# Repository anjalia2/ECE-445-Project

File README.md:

# Circle of Life: Automated Desktop Aquaponics System

## Team Members: Anjali Aravindhan, Aishwarya Manoj, Estela Medrano-Gutierrez

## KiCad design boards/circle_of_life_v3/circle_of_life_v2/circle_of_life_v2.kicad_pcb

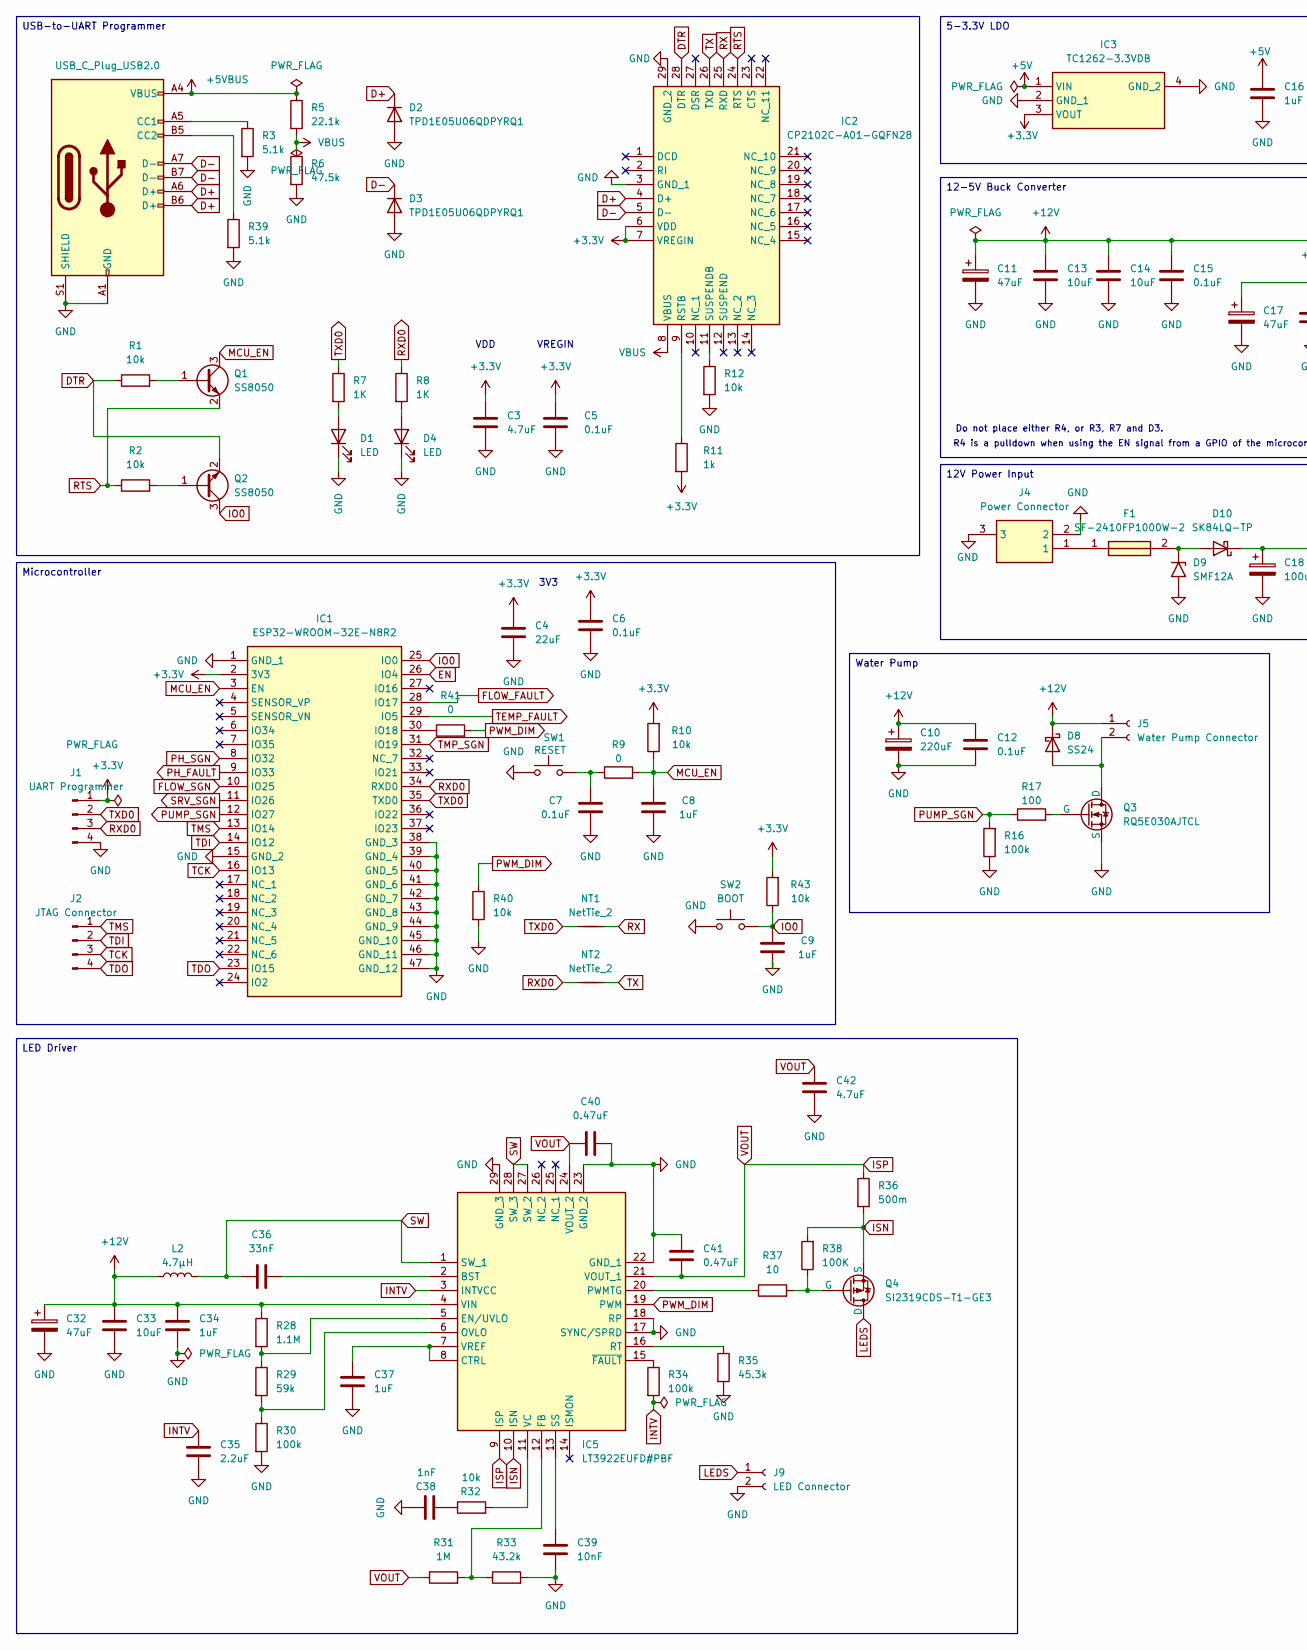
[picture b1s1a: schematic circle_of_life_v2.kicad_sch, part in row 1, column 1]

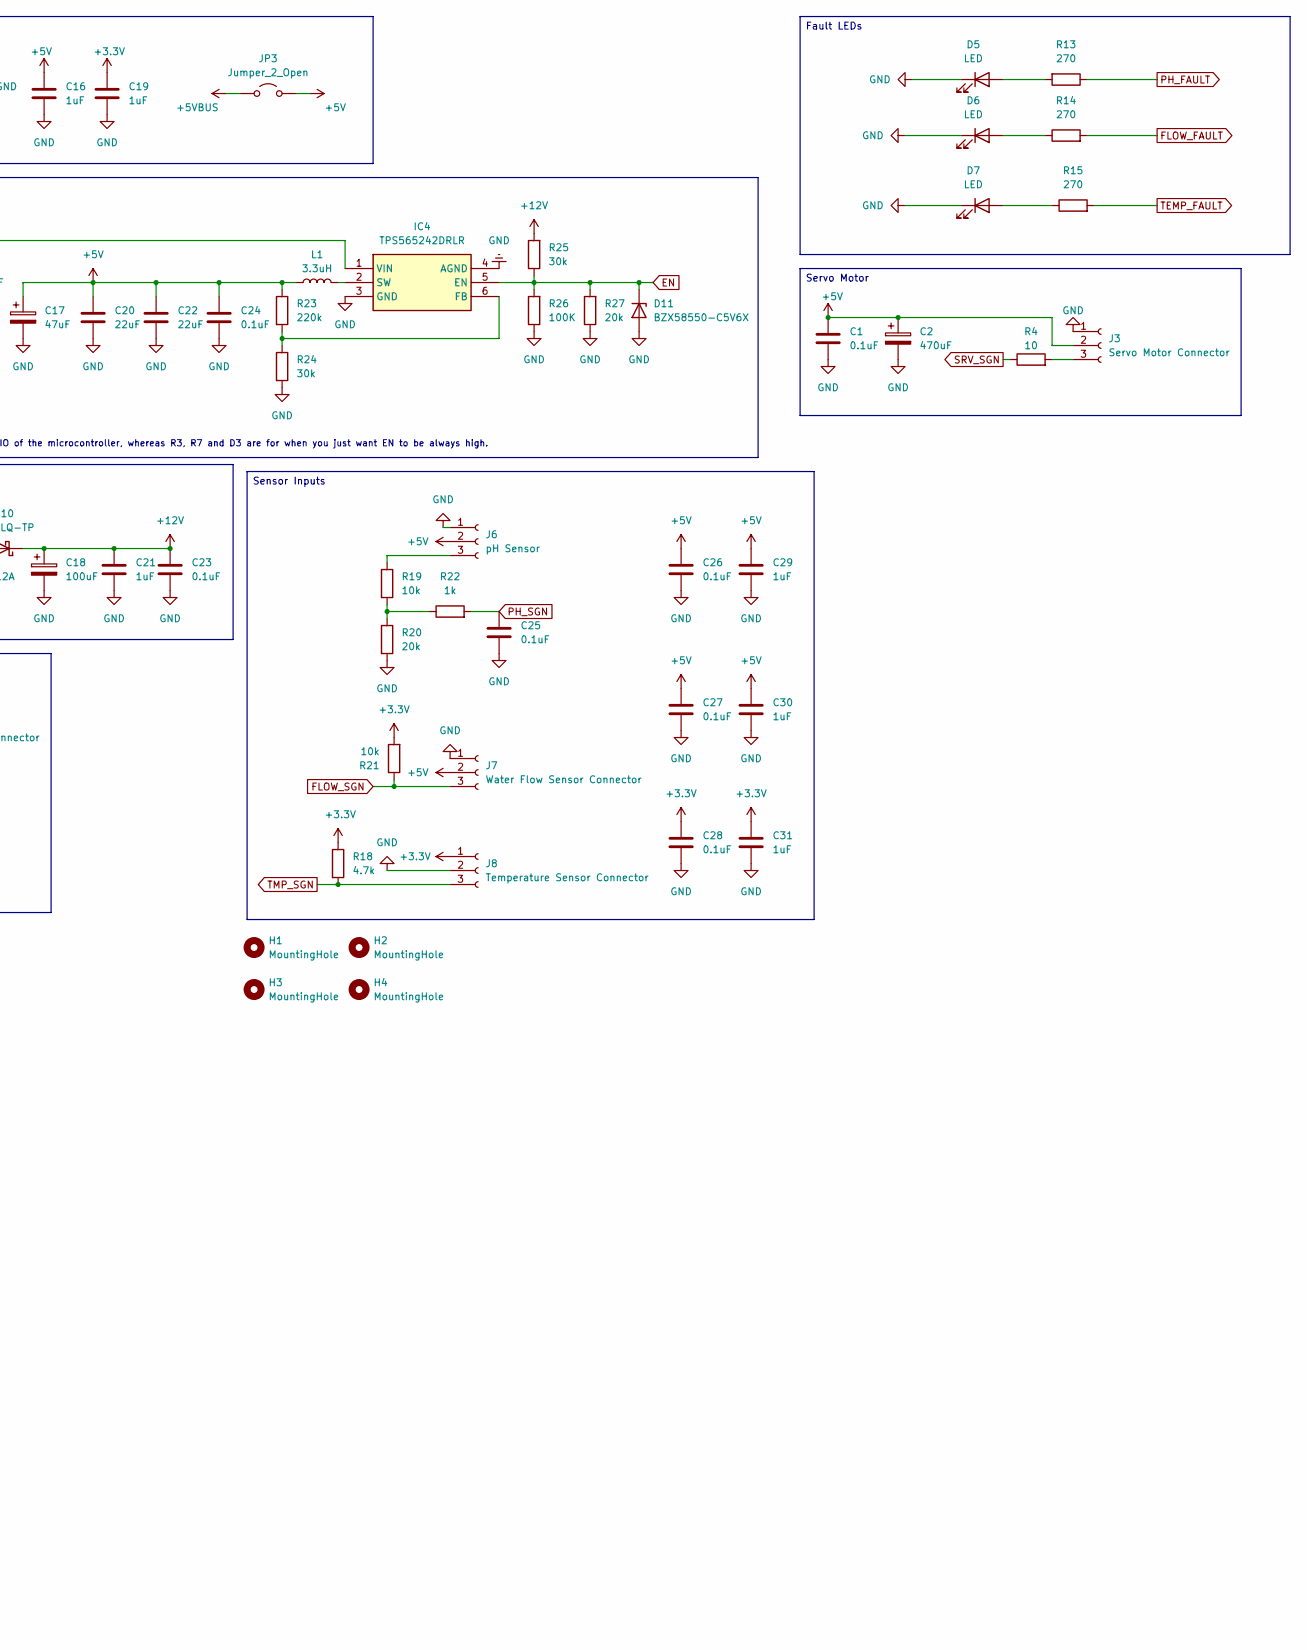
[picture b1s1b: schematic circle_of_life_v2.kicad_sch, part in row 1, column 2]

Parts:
C1, C5, C6, C7, C12, C23, C24, C25, C26, C27, C28: 0.1uF; C_0805_2012Metric
C2: 470uF; CAPPRD500W60D1025H1400
C3, C42: 4.7uF; C_0805_2012Metric
C4, C20, C22: 22uF; CAPC3216X190N
C8, C9, C16, C19, C21, C29, C30, C31, C34, C37: 1uF; C_0805_2012Metric
C10: 220uF; CAPPRD350W60D825H1300
C11, C17, C32: 47uF; CAPPRD250W50D655H1250
C13, C14: 10uF; C_0805_2012Metric
C15: 0.1uF; C_0805_2012Metric_Pad1.18x1.45mm_HandSolder
C18: 100uF; CAPAE630X800N
C33: 10uF; R_0805_2012Metric_Pad1.20x1.40mm_HandSolder
C35: 2.2uF; CAPC1608X90N
C36: 33nF; 0805_AVX
C38: 1nF; C_0805_2012Metric
C39: 10nF; C_0603_1608Metric
C40, C41: 0.47uF; GRM15x
D1, D4: LED; LED_0603_1608Metric
D2, D3: TPD1E05U06QDPYRQ1; DPY_R-PX1SON-N2_
D5, D6, D7: LED; LED_D5.0mm
D8: SS24; DIOM5436X247N
D9: SMF12A; TVS_SMF12A
D10: SK84LQ-TP; DIOM7959X262N
D11: BZX58550-C5V6X; D_SOD-523
F1: SF-2410FP1000W-2; FUSC6125X236N; Mouser Part Number 652-SF-2410FP1000W-2
H1, H2, H3, H4: MountingHole; MountingHole_3.2mm_M3_ISO7380
IC1: ESP32-WROOM-32E-N8R2; ESP32WROOM32EN8R2; Mouser Part Number 356-ESP32WRM32EN8R2
IC2: CP2102C-A01-GQFN28; QFN50P500X500X80-29N-D; Mouser Part Number 634-P2102CA01GQFN28
IC3: TC1262-3.3VDB; SOT230P700X180-4N; Mouser Part Number 579-TC1262-3.3VDB
IC4: TPS565242DRLR; SOTFL50P160X60-6N; Mouser Part Number 595-TPS565242DRLR
IC5: LT3922EUFD#PBF; QFN50P400X500X80-29N-D; Mouser Part Number 584-LT3922EUFD#PBF
J1: UART Programmer; PinHeader_1x04_P2.54mm_Vertical
J2: JTAG Connector; PinHeader_1x04_P2.54mm_Vertical
J3: Servo Motor Connector; 691137710003
J4: Power Connector; 694108301002; Mouser Part Number 710-694108301002
J5: Water Pump Connector; 2828372
J6: pH Sensor; 691137710003
J7: Water Flow Sensor Connector; 691137710003
J8: Temperature Sensor Connector; 691137710003
J9: LED Connector; 2828372
JP3: Jumper_2_Open; SolderJumper-2_P1.3mm_Open_RoundedPad1.0x1.5mm
L1: 3.3uH; INDC4949X330N
L2: 4.7µH; SRN6045_1
NT1, NT2: NetTie_2; NetTie-2_SMD_Pad0.5mm
P1: USB_C_Plug_USB2.0; USB_C_Receptacle_HRO_TYPE-C-31-M-12
Q1, Q2: SS8050; SOT-23
Q3: RQ5E030AJTCL; SOT95P280X100-3N
Q4: SI2319CDS-T1-GE3; SOT95P237X112-3N
R1, R2, R12, R43: 10k; R_0603_1608Metric
R3, R39: 5.1k; R_0603_1608Metric
R4, R37: 10; RESC1608X55N
R5: 22.1k; R_0603_1608Metric
R6: 47.5k; R_0603_1608Metric
R7, R8: 1K; RESC1608X55N
R9, R41: 0; RESC1608X55N
R10, R19, R21, R32, R40: 10k; RESC1608X55N
R11: 1k; R_0603_1608Metric
R13, R14, R15: 270; RESC1608X55N
R16, R34: 100k; RESC1608X55N
R17: 100; RESC1608X55N
R18: 4.7k; RESC1608X55N
R20: 20k; RESC1608X55N
R22: 1k; RESC1608X55N
R23: 220k; RESC2012X60N
R24: 30k; RESC2012X60N
R25: 30k; R_0805_2012Metric
R26: 100K; RESC2012X60N
R27: 20k; RESC2012X60N
R28: 1.1M; RESC3116X65N
R29: 59k; RESC2012X60N
R30: 100k; RESC2012X60N
R31: 1M; RESC1608X55N
R33: 43.2k; RESC1608X55N
R35: 45.3k; RESC1608X55N
R36: 500m; CSR1206
R38: 100K; RESC1608X55N
SW1: RESET; SW_SPST_SKQG_WithStem
SW2: BOOT; SW_SPST_SKQG_WithStem

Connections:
+3.3V: C3.1, C4.1, C5.1, C6.1, C19.1, C28.1, C31.1, IC1.2 (3V3), IC2.6 (VDD), IC2.7 (VREGIN), IC3.3 (VOUT), J1.1, J8.1, R10.2, R11.2, R18.1, R21.2, R43.2
+5V: C1.1, C2.1, C16.1, C17.1, C20.1, C22.1, C24.1, C26.1, C27.1, C29.1, C30.1, IC3.1 (VIN), J3.2, J6.2, J7.2, JP3.2 (B), L1.1, R23.1
+5VBUS: JP3.1 (A), P1.A4 (VBUS), P1.A9 (VBUS), P1.B4 (VBUS), P1.B9 (VBUS), R5.1
+12V: C10.1, C11.1, C12.1, C13.1, C14.1, C15.1, C18.1, C21.1, C23.1, C32.1, C33.2, C34.2, D8.1 (K), D10.1 (K), IC4.1 (VIN), IC5.4 (VIN), J5.1, L2.1, R25.2, R28.1
D+: D2.1 (K), IC2.4 (D+), P1.A6 (D+), P1.B6 (D+)
D-: D3.1 (K), IC2.5 (D-), P1.A7 (D-), P1.B7 (D-)
DTR: IC2.28 (DTR), Q2.2 (E), R1.1
EN: D11.1 (K), IC1.26 (IO4), IC4.5 (EN), R25.1, R26.2, R27.2
FLOW_FAULT: IC1.28 (IO17), R14.2
FLOW_SGN: IC1.10 (IO25), J7.3, R21.1
GND: C1.2, C2.2, C3.2, C4.2, C5.2, C6.2, C7.1, C8.1, C9.1, C10.2, C11.2, C12.2, C13.2, C14.2, C15.2, C16.2, C17.2, C18.2, C19.2, C20.2, C21.2, C22.2, C23.2, C24.2, C25.2, C26.2, C27.2, C28.2, C29.2, C30.2, C31.2, C32.2, C33.1, C34.1, C35.2, C37.1, C38.2, C39.1, C40.2, C41.2, C42.2, D1.1 (K), D2.2 (A), D3.2 (A), D4.1 (K), D5.1 (K), D6.1 (K), D7.1 (K), D9.2 (A2), D11.2 (A), IC1.1 (GND_1), IC1.15 (GND_2), IC1.38 (GND_3), IC1.39 (GND_4), IC1.40 (GND_5), IC1.41 (GND_6), IC1.42 (GND_7), IC1.43 (GND_8), IC1.44 (GND_9), IC1.45 (GND_10), IC1.46 (GND_11), IC1.47 (GND_12), IC2.3 (GND_1), IC2.29 (GND_2), IC3.2 (GND_1), IC3.4 (GND_2), IC4.3 (GND), IC4.4 (AGND), IC5.17 (SYNC/SPRD), IC5.18 (RP), IC5.22 (GND_1), IC5.23 (GND_2), IC5.29 (GND_3), J1.4, J3.1, J4.2, J4.3, J6.1, J7.1, J8.2, J9.2, P1.A1 (GND), P1.A12 (GND), P1.B1 (GND), P1.B12 (GND), P1.S1 (SHIELD), Q3.3 (S), R3.2, R6.2, R12.2, R16.1, R20.2, R24.2, R26.1, R27.1, R30.2, R33.2, R35.2, R39.2, R40.2, SW1.1, SW2.1
INTV: C35.1, IC5.3 (INTVCC), R34.2
IO0: C9.2, IC1.25 (IO0), Q2.3 (C), R43.1, SW2.2
ISN: IC5.10 (ISN), Q4.3 (S), R36.2, R38.2
ISP: C40.1, C41.1, C42.1, IC5.9 (ISP), IC5.21 (VOUT_1), IC5.24 (VOUT_2), R31.1, R36.1
LEDS: J9.1, Q4.1 (D)
MCU_EN: C8.2, IC1.3 (EN), Q1.3 (C), R9.2, R10.1
unnamed: C7.2, R9.1, SW1.2
unnamed: C38.1, R32.1
unnamed: D1.2 (A), R7.2
unnamed: D4.2 (A), R8.2
unnamed: D5.2 (A), R13.2
unnamed: D6.2 (A), R14.1
unnamed: D7.2 (A), R15.1
unnamed: D8.2 (A), J5.2, Q3.1 (D)
unnamed: D9.1 (A1), D10.2 (A), F1.2
unnamed: F1.1, J4.1
unnamed: IC1.30 (IO18), R41.1
unnamed: IC2.9 (RSTB), R11.1
unnamed: IC2.11 (SUSPENDB), R12.1
unnamed: IC4.6 (FB), R23.2, R24.1
unnamed: IC4.2 (SW), L1.2
unnamed: C36.2, IC5.2 (BST)
unnamed: C37.2, IC5.7 (VREF), IC5.8 (CTRL)
unnamed: IC5.5 (EN/UVLO), R28.2, R29.1
unnamed: IC5.12 (FB), R31.2, R33.1
unnamed: IC5.6 (OVLO), R29.2, R30.1
unnamed: IC5.20 (PWMTG), R37.1
unnamed: IC5.16 (RT), R35.1
unnamed: C39.2, IC5.13 (SS)
unnamed: IC5.11 (VC), R32.2
unnamed: IC5.15 (~FAULT), R34.1
unnamed: J3.3, R4.2
unnamed: J6.3, R19.1
unnamed: P1.A5 (CC1), R3.1
unnamed: P1.B5 (CC2), R39.1
unnamed: Q1.1 (B), R1.2
unnamed: Q2.1 (B), R2.2
unnamed: Q3.2 (G), R17.2
unnamed: Q4.2 (G), R37.2, R38.1
unnamed: R19.2, R20.1, R22.1
PH_FAULT: IC1.9 (IO33), R13.1
PH_SGN: C25.1, IC1.8 (IO32), R22.2
PUMP_SGN: IC1.12 (IO27), R16.2, R17.1
PWM_DIM: IC5.19 (PWM), R40.1, R41.2
RTS: IC2.24 (RTS), Q1.2 (E), R2.1
RX: IC2.25 (RXD), NT1.2
RXD0: IC1.34 (RXD0), J1.3, NT2.1, R8.1
SRV_SGN: IC1.11 (IO26), R4.1
SW: C36.1, IC5.1 (SW_1), IC5.27 (SW_2), IC5.28 (SW_3), L2.2
TCK: IC1.16 (IO13), J2.3
TDI: IC1.14 (IO12), J2.2
TDO: IC1.23 (IO15), J2.4
TEMP_FAULT: IC1.29 (IO5), R15.2
TMP_SGN: IC1.31 (IO19), J8.3, R18.2
TMS: IC1.13 (IO14), J2.1
TX: IC2.26 (TXD), NT2.2
TXD0: IC1.35 (TXD0), J1.2, NT1.1, R7.1
VBUS: IC2.8 (VBUS), R5.2, R6.1

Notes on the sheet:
R4 is a pulldown when using the EN signal from a GPIO of the microcontroller, whereas R3, R7 and D3 are for when you just want EN to be always high.
Do not place either R4, or R3, R7 and D3.
VDD
3V3
VREGIN
5-3.3V LDO
Sensor Inputs
12V Power Input
Fault LEDs
USB-to-UART Programmer
LED Driver
Servo Motor
Microcontroller
Water Pump
12-5V Buck Converter

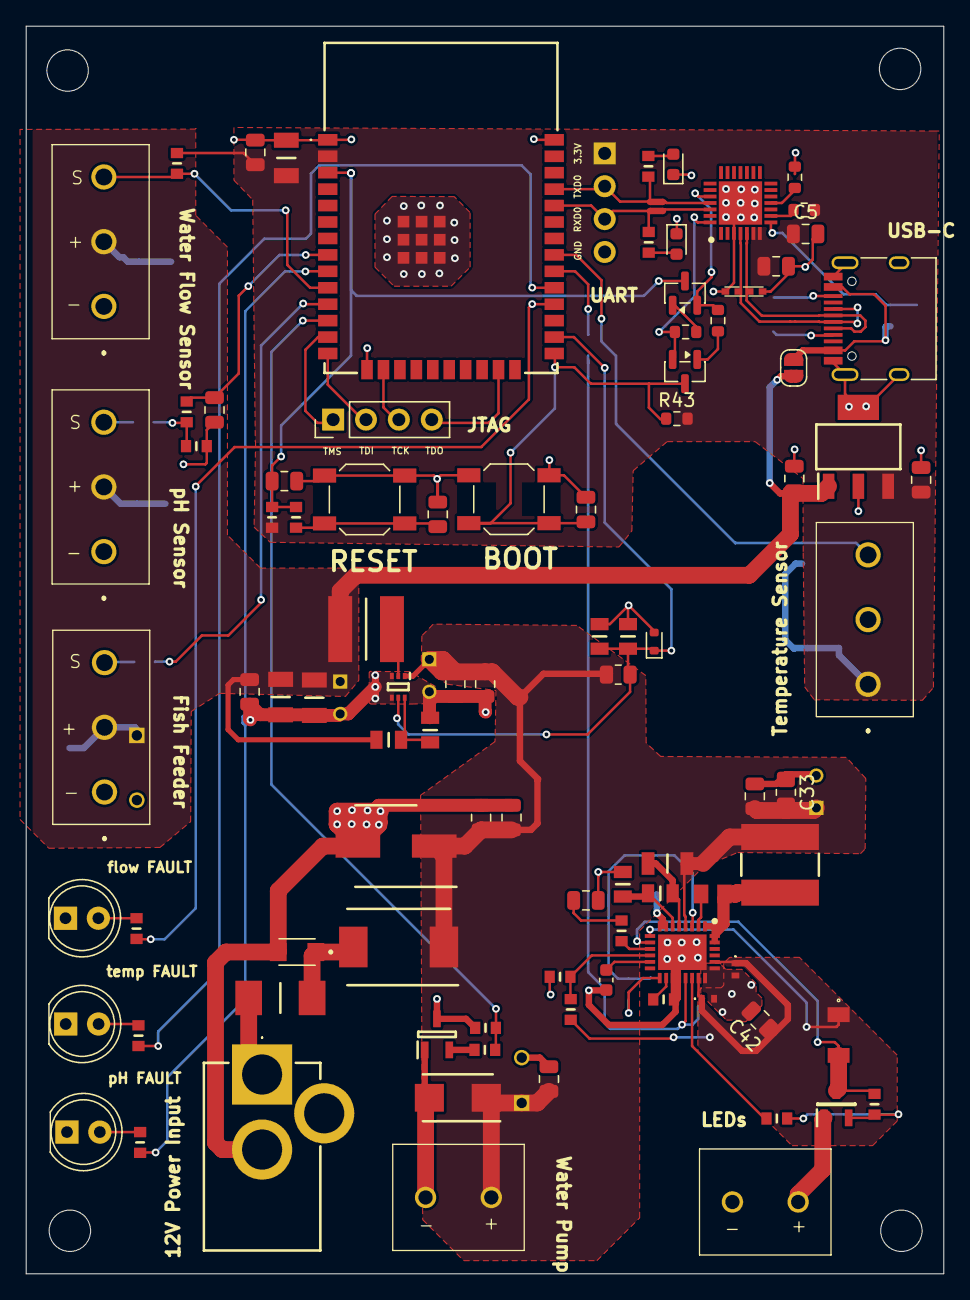
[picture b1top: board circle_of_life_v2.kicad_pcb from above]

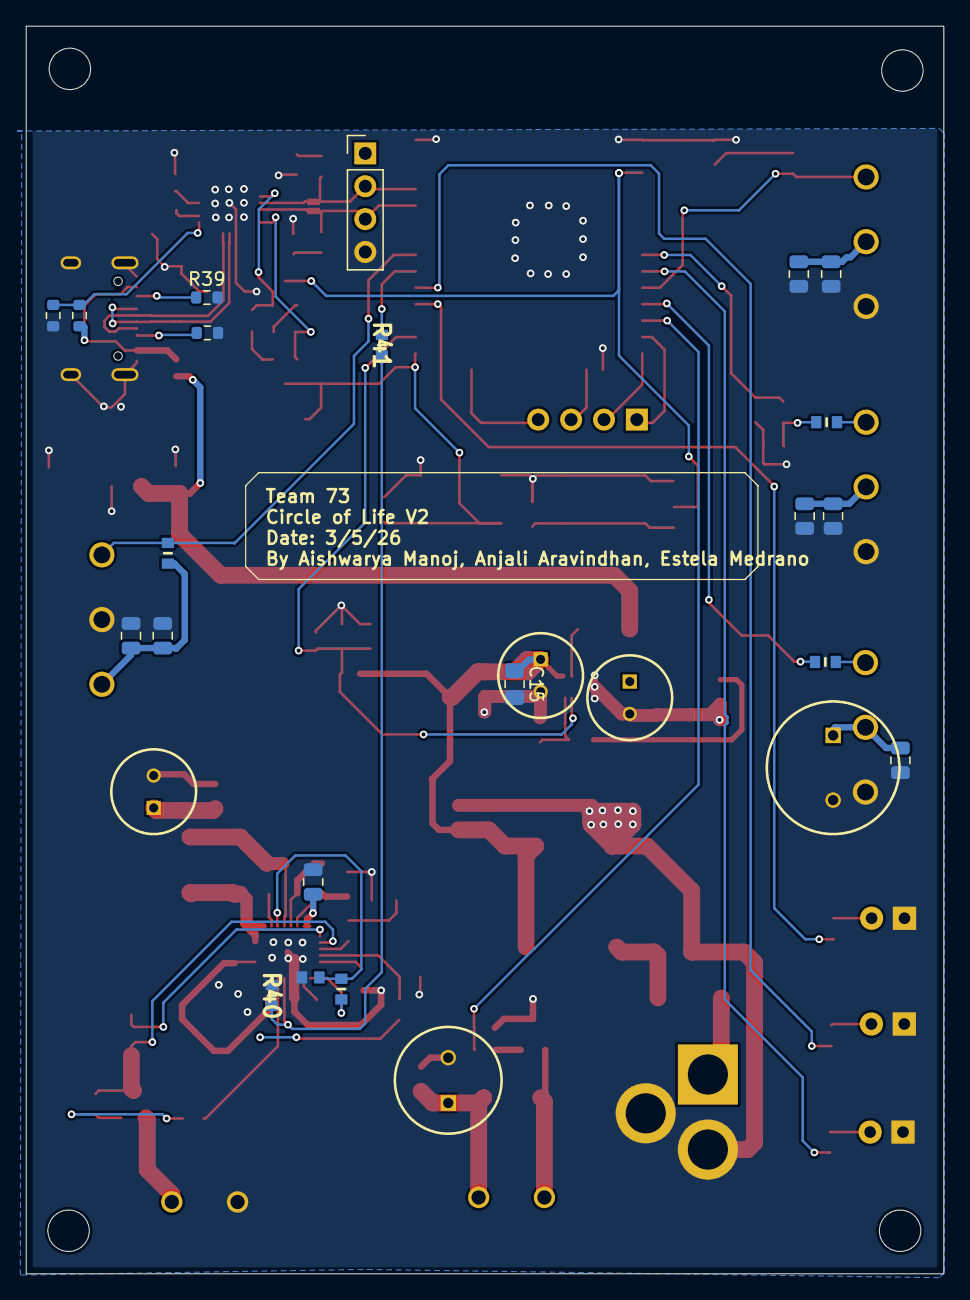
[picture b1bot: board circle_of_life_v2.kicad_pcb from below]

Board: 2 copper layers, 70.9 x 96.4 mm, 126 parts (26 on the bottom side), 69 nets.

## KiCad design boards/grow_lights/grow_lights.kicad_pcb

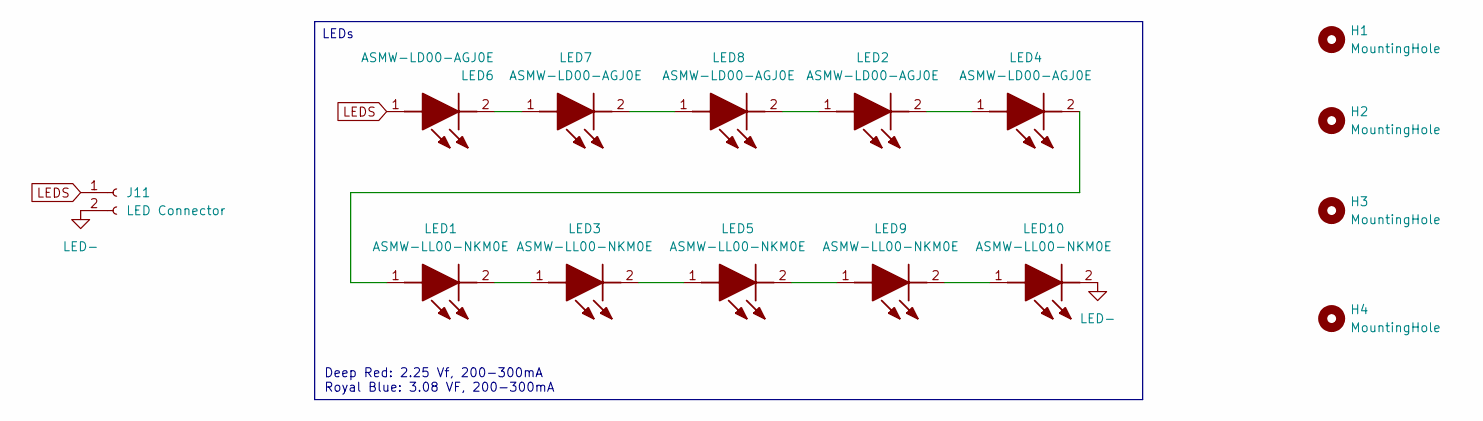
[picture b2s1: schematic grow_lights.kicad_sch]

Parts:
H1, H2, H3, H4: MountingHole; MountingHole_3.2mm_M3
J11: LED Connector; 2828372
LED1, LED3, LED5, LED9, LED10: ASMW-LL00-NKM0E; ASMWLL00NKM0E; Mouser Part Number 630-ASMW-LL00-NKM0E
LED2, LED4, LED6, LED7, LED8: ASMW-LD00-AGJ0E; ASMWLL00NKM0E; Mouser Part Number 630-ASMW-LL00-NKM0E

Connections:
LED-: J11.2, LED10.2 (K)
LEDS: J11.1, LED6.1 (A)
unnamed: LED1.1 (A), LED4.2 (K)
unnamed: LED1.2 (K), LED3.1 (A)
unnamed: LED2.1 (A), LED8.2 (K)
unnamed: LED2.2 (K), LED4.1 (A)
unnamed: LED3.2 (K), LED5.1 (A)
unnamed: LED5.2 (K), LED9.1 (A)
unnamed: LED6.2 (K), LED7.1 (A)
unnamed: LED7.2 (K), LED8.1 (A)
unnamed: LED9.2 (K), LED10.1 (A)

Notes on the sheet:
Deep Red: 2.25 Vf, 200-300mA Royal Blue: 3.08 VF, 200-300mA
LEDs

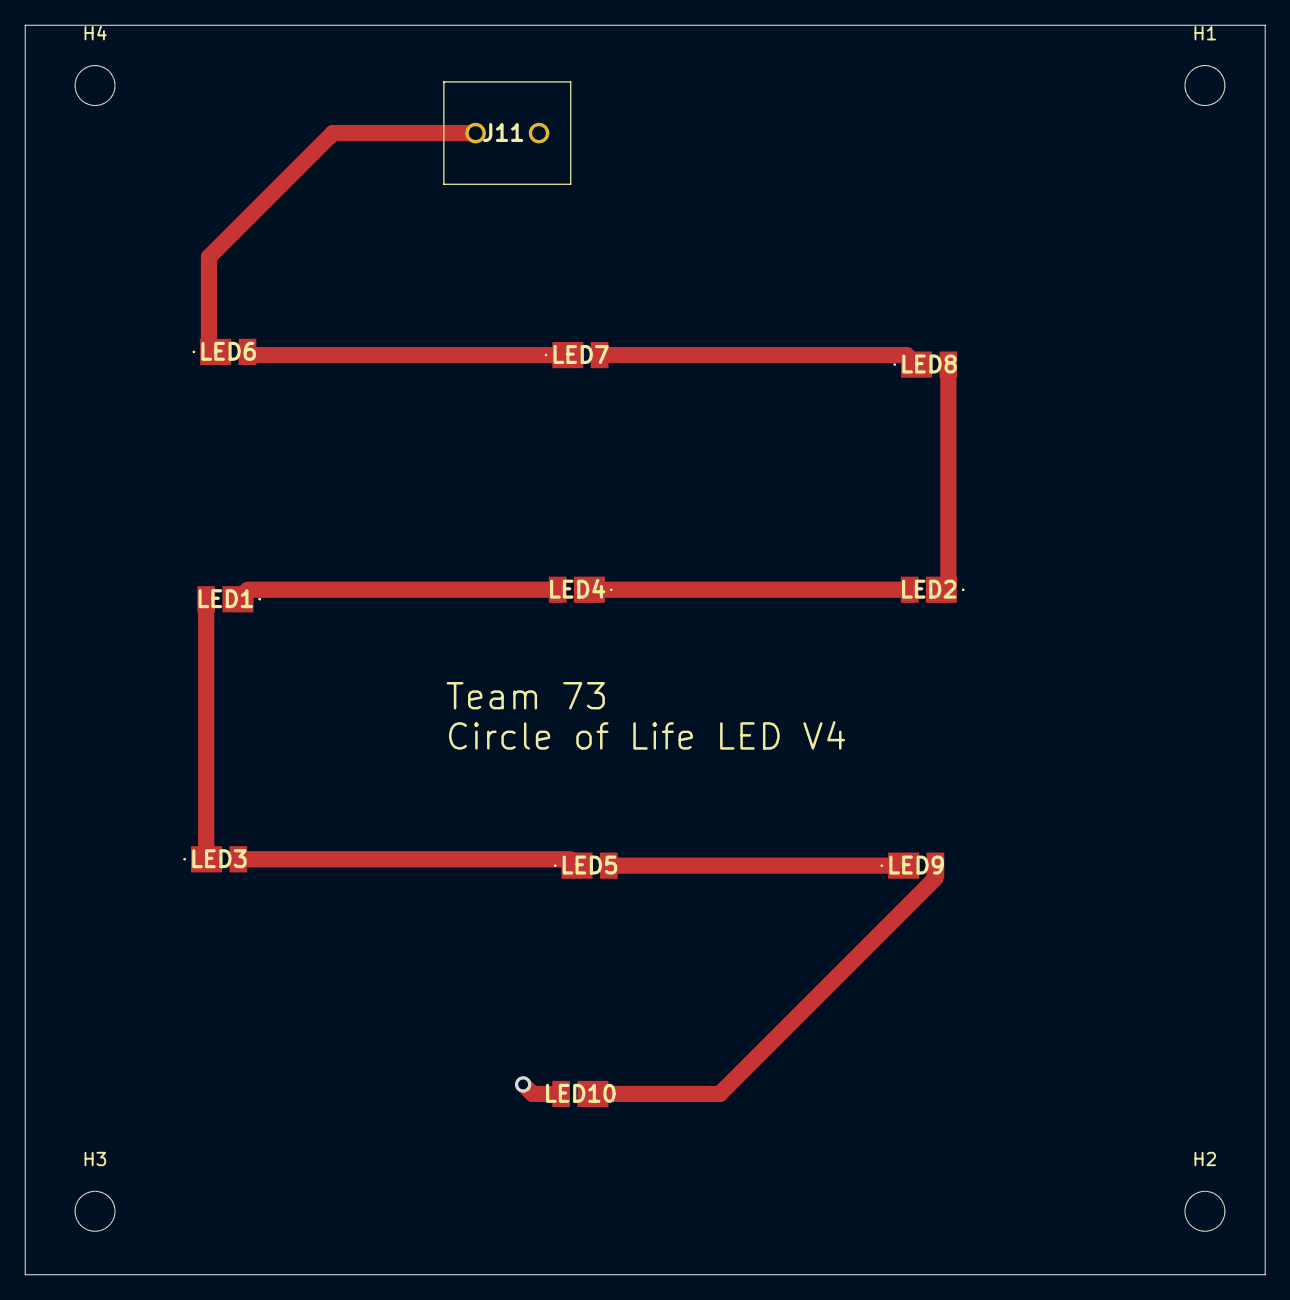
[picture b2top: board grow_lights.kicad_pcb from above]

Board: 2 copper layers, 99.3 x 100.1 mm, 15 parts (0 on the bottom side), 11 nets.

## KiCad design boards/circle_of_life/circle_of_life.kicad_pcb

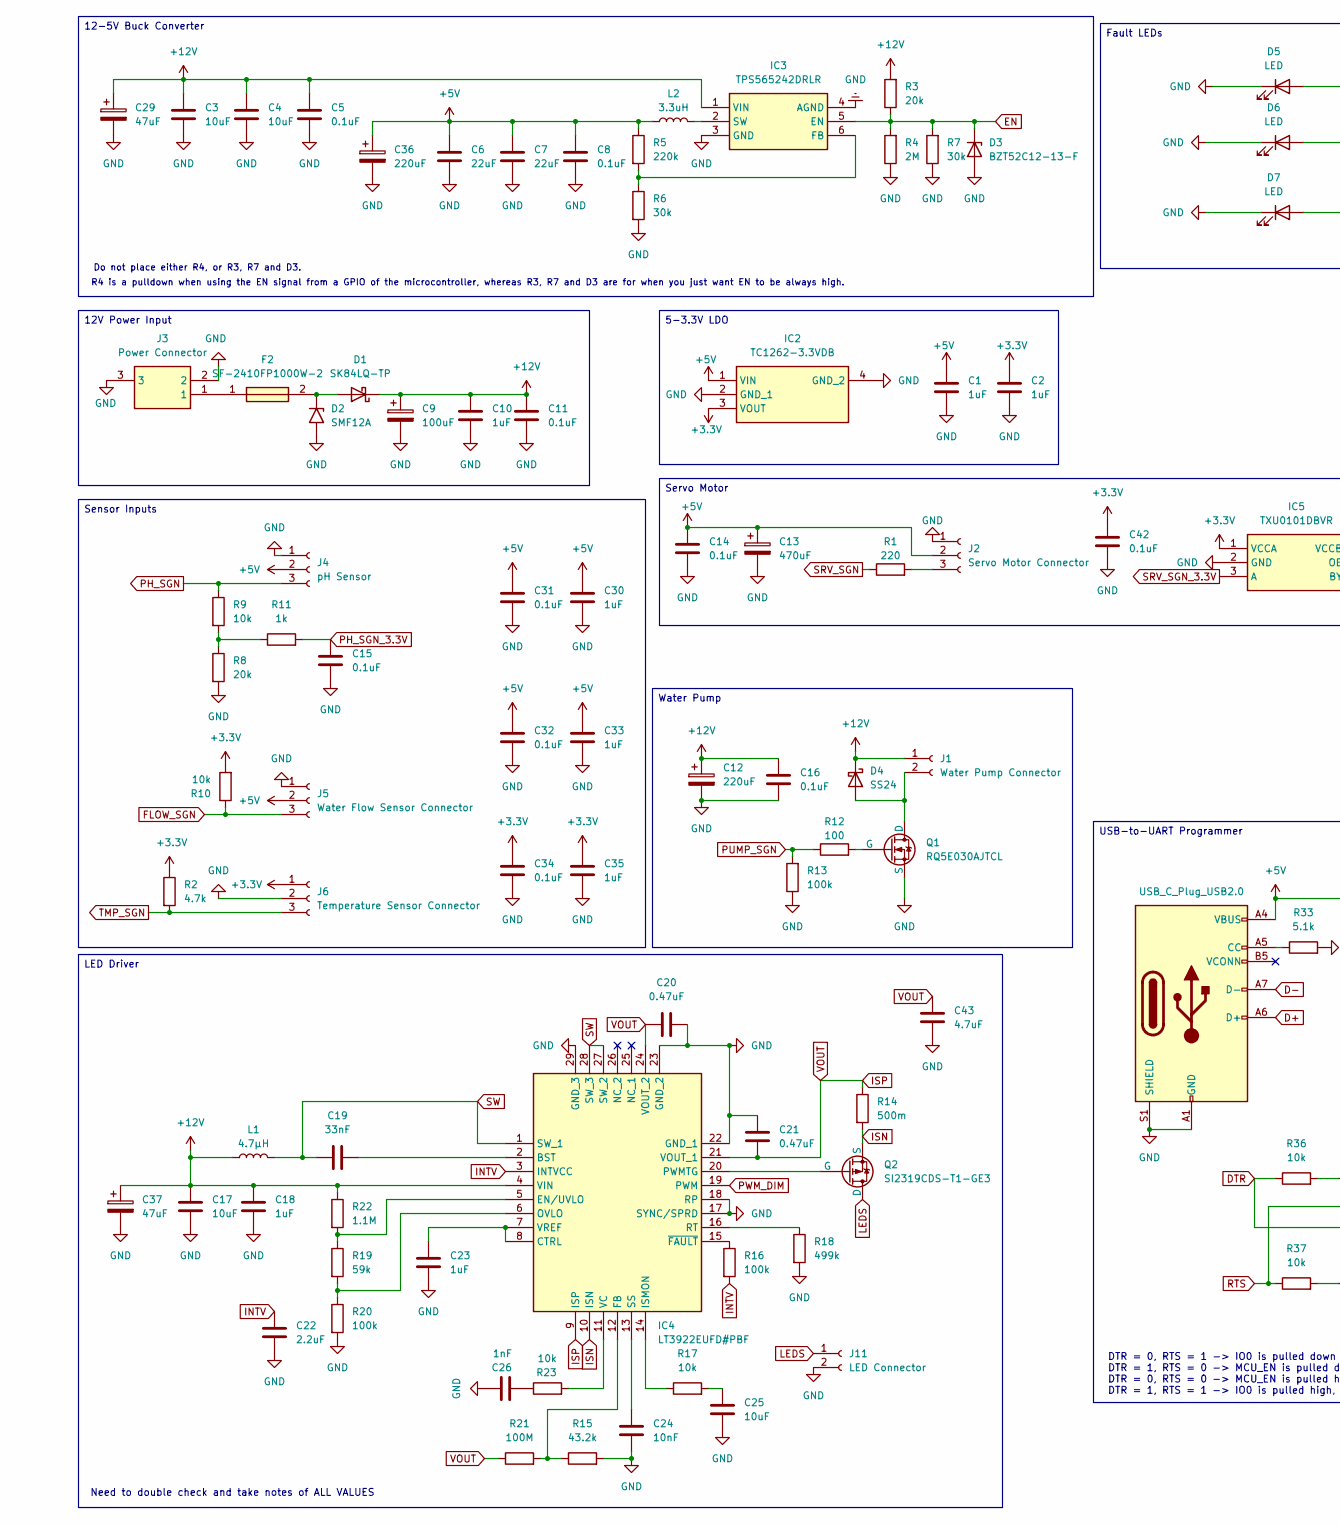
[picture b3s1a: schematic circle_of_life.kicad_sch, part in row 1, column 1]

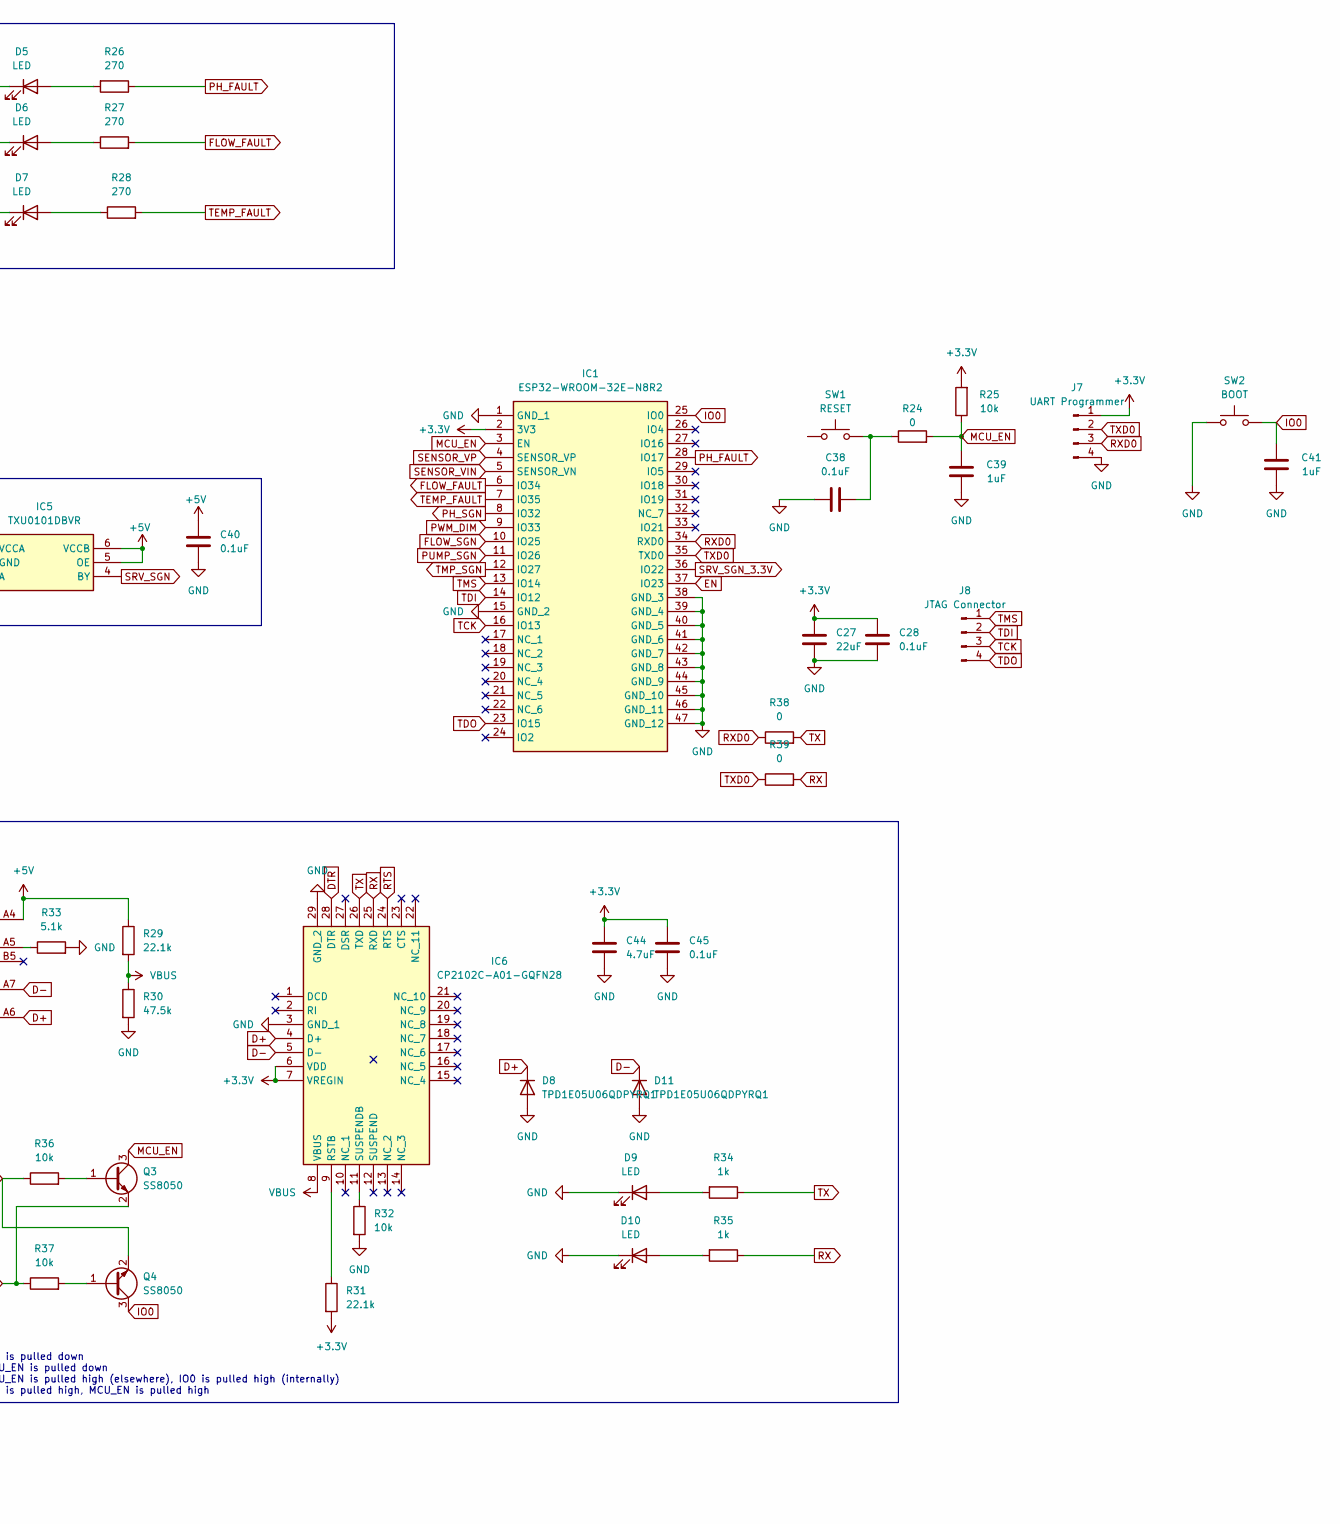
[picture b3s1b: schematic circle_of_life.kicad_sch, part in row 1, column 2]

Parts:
C1, C2, C10, C18, C23, C30, C33, C35, C39, C41: 1uF; C_0805_2012Metric
C3, C4, C25: 10uF; C_0805_2012Metric
C5, C8, C11, C14, C15, C16, C28, C31, C32, C34, C38, C40: 0.1uF; C_0805_2012Metric
C6, C7, C27: 22uF; CAPC3216X190N
C9: 100uF; CAPAE630X800N
C12, C36: 220uF; CAPPRD350W60D825H1300
C13: 470uF; CAPPRD500W60D1025H1400
C17: 10uF; CAPC3216X180N
C19: 33nF; 0805_AVX
C20, C21: 0.47uF; GRM15x
C22: 2.2uF; CAPC1608X90N
C24: 10nF; C_0603_1608Metric
C26: 1nF; C_0805_2012Metric
C29, C37: 47uF; CAPPRD250W50D655H1250
C42, C45: 0.1uF; C_0603_1608Metric
C43: 4.7uF; C_1206_3216Metric
C44: 4.7uF; C_0805_2012Metric
D1: SK84LQ-TP; DIOM7959X262N
D2: SMF12A; TVS_SMF12A
D3: BZT52C12-13-F; SOD3716X145N
D4: SS24; DIOM5436X247N
D5, D6, D7: LED; LED_D5.0mm
D8, D11: TPD1E05U06QDPYRQ1; DPY_R-PX1SON-N2_
D9, D10: LED; LED_0603_1608Metric
F2: SF-2410FP1000W-2; FUSC6125X236N; Mouser Part Number 652-SF-2410FP1000W-2
IC1: ESP32-WROOM-32E-N8R2; ESP32WROOM32EN8R2; Mouser Part Number 356-ESP32WRM32EN8R2
IC2: TC1262-3.3VDB; SOT230P700X180-4N; Mouser Part Number 579-TC1262-3.3VDB
IC3: TPS565242DRLR; SOTFL50P160X60-6N; Mouser Part Number 595-TPS565242DRLR
IC4: LT3922EUFD#PBF; QFN50P400X500X80-29N-D; Mouser Part Number 584-LT3922EUFD#PBF
IC5: TXU0101DBVR; SOT95P280X145-6N; Mouser Part Number 595-TXU0101DBVR
IC6: CP2102C-A01-GQFN28; QFN50P500X500X80-29N-D; Mouser Part Number 634-P2102CA01GQFN28
J1: Water Pump Connector; 2828372
J2: Servo Motor Connector; 691137710003
J3: Power Connector; 694108301002; Mouser Part Number 710-694108301002
J4: pH Sensor; 691137710003
J5: Water Flow Sensor Connector; 691137710003
J6: Temperature Sensor Connector; 691137710003
J7: UART Programmer; PinHeader_1x04_P2.54mm_Vertical
J8: JTAG Connector; PinHeader_1x04_P2.54mm_Vertical
J11: LED Connector; 2828372
L1: 4.7µH; SRN6045_1
L2: 3.3uH; INDC4949X330N
P1: USB_C_Plug_USB2.0; USB_C_Receptacle_HRO_TYPE-C-31-M-12
Q1: RQ5E030AJTCL; SOT95P280X100-3N
Q2: SI2319CDS-T1-GE3; SOT95P237X112-3N
Q3, Q4: SS8050; SOT-23
R1: 220; RESC1608X55N
R2: 4.7k; RESC1608X55N
R3: 20k; R_0805_2012Metric
R4: 2M; RESC2012X60N
R5: 220k; RESC2012X60N
R6, R7: 30k; RESC2012X60N
R8: 20k; RESC1608X55N
R9, R10, R17, R23, R25: 10k; RESC1608X55N
R11, R34, R35: 1k; RESC1608X55N
R12: 100; RESC1608X55N
R13, R16: 100k; RESC1608X55N
R14: 500m; CSR1206
R15: 43.2k; RESC1608X55N
R18: 499k; RESC1608X55N
R19: 59k; RESC2012X60N
R20: 100k; RESC2012X60N
R21: 100M; RESC1608X55N
R22: 1.1M; RESC3116X65N
R24: 0; RESC1608X55N
R26, R27, R28: 270; RESC1608X55N
R29, R31: 22.1k; R_0603_1608Metric
R30: 47.5k; R_0603_1608Metric
R32, R36, R37: 10k; R_0603_1608Metric
R33: 5.1k; R_0603_1608Metric
R38, R39: 0; R_0603_1608Metric
SW1: RESET; SW_SPST_SKQG_WithStem
SW2: BOOT; SW_SPST_SKQG_WithStem

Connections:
+3.3V: C2.1, C27.1, C28.1, C34.1, C35.1, C42.1, C44.1, C45.1, IC1.2 (3V3), IC2.3 (VOUT), IC5.1 (VCCA), IC6.6 (VDD), IC6.7 (VREGIN), J6.1, J7.1, R2.1, R10.2, R25.2, R31.2
+5V: C1.1, C6.1, C7.1, C8.1, C13.1, C14.1, C30.1, C31.1, C32.1, C33.1, C36.1, C40.1, IC2.1 (VIN), IC5.5 (OE), IC5.6 (VCCB), J2.2, J4.2, J5.2, L2.1, P1.A4 (VBUS), P1.A9 (VBUS), P1.B4 (VBUS), P1.B9 (VBUS), R5.1, R29.1
+12V: C3.1, C4.1, C5.1, C9.1, C10.1, C11.1, C12.1, C16.1, C17.2, C18.2, C29.1, C37.1, D1.1 (K), D4.1 (K), IC3.1 (VIN), IC4.4 (VIN), J1.1, L1.1, R3.2, R22.1
D+: D8.1 (K), IC6.4 (D+), P1.A6 (D+)
D-: D11.1 (K), IC6.5 (D-), P1.A7 (D-)
DTR: IC6.28 (DTR), Q4.2 (E), R36.1
EN: D3.1 (K), IC1.37 (IO23), IC3.5 (EN), R3.1, R4.2, R7.2
FLOW_FAULT: IC1.6 (IO34), R27.2
FLOW_SGN: IC1.10 (IO25), J5.3, R10.1
GND: C1.2, C2.2, C3.2, C4.2, C5.2, C6.2, C7.2, C8.2, C9.2, C10.2, C11.2, C12.2, C13.2, C14.2, C15.2, C16.2, C17.1, C18.1, C20.2, C21.2, C22.2, C23.1, C24.1, C25.1, C26.2, C27.2, C28.2, C29.2, C30.2, C31.2, C32.2, C33.2, C34.2, C35.2, C36.2, C37.2, C38.1, C39.1, C40.2, C41.1, C42.2, C43.2, C44.2, C45.2, D2.2 (A2), D3.2 (A), D5.1 (K), D6.1 (K), D7.1 (K), D8.2 (A), D9.1 (K), D10.1 (K), D11.2 (A), IC1.1 (GND_1), IC1.15 (GND_2), IC1.38 (GND_3), IC1.39 (GND_4), IC1.40 (GND_5), IC1.41 (GND_6), IC1.42 (GND_7), IC1.43 (GND_8), IC1.44 (GND_9), IC1.45 (GND_10), IC1.46 (GND_11), IC1.47 (GND_12), IC2.2 (GND_1), IC2.4 (GND_2), IC3.3 (GND), IC3.4 (AGND), IC4.17 (SYNC/SPRD), IC4.18 (RP), IC4.22 (GND_1), IC4.23 (GND_2), IC4.29 (GND_3), IC5.2 (GND), IC6.3 (GND_1), IC6.29 (GND_2), J2.1, J3.2, J3.3, J4.1, J5.1, J6.2, J7.4, J11.2, P1.A1 (GND), P1.A12 (GND), P1.B1 (GND), P1.B12 (GND), P1.S1 (SHIELD), Q1.3 (S), R4.1, R6.2, R7.1, R8.2, R13.1, R15.2, R18.2, R20.2, R30.2, R32.2, R33.2, SW2.1
INTV: C22.1, IC4.3 (INTVCC), R16.2
IO0: C41.2, IC1.25 (IO0), Q4.3 (C), SW2.2
ISN: IC4.10 (ISN), Q2.3 (S), R14.2
ISP: C20.1, C21.1, C43.1, IC4.9 (ISP), IC4.21 (VOUT_1), IC4.24 (VOUT_2), R14.1, R21.1
LEDS: J11.1, Q2.1 (D)
MCU_EN: C39.2, IC1.3 (EN), Q3.3 (C), R24.2, R25.1
unnamed: C25.2, R17.2
unnamed: C26.1, R23.1
unnamed: C38.2, R24.1, SW1.2
unnamed: D1.2 (A), D2.1 (A1), F2.2
unnamed: D4.2 (A), J1.2, Q1.1 (D)
unnamed: D5.2 (A), R26.2
unnamed: D6.2 (A), R27.1
unnamed: D7.2 (A), R28.1
unnamed: D9.2 (A), R34.2
unnamed: D10.2 (A), R35.2
unnamed: F2.1, J3.1
unnamed: IC3.6 (FB), R5.2, R6.1
unnamed: IC3.2 (SW), L2.2
unnamed: C19.2, IC4.2 (BST)
unnamed: C23.2, IC4.7 (VREF), IC4.8 (CTRL)
unnamed: IC4.5 (EN/UVLO), R19.1, R22.2
unnamed: IC4.12 (FB), R15.1, R21.2
unnamed: IC4.14 (ISMON), R17.1
unnamed: IC4.6 (OVLO), R19.2, R20.1
unnamed: IC4.20 (PWMTG), Q2.2 (G)
unnamed: IC4.16 (RT), R18.1
unnamed: C24.2, IC4.13 (SS)
unnamed: IC4.11 (VC), R23.2
unnamed: IC4.15 (~FAULT), R16.1
unnamed: IC6.9 (RSTB), R31.1
unnamed: IC6.11 (SUSPENDB), R32.1
unnamed: J2.3, R1.2
unnamed: P1.A5 (CC), R33.1
unnamed: Q1.2 (G), R12.2
unnamed: Q3.1 (B), R36.2
unnamed: Q4.1 (B), R37.2
unnamed: R8.1, R9.2, R11.1
PH_FAULT: IC1.28 (IO17), R26.1
PH_SGN: IC1.8 (IO32), J4.3, R9.1
PH_SGN_3.3V: C15.1, R11.2
PUMP_SGN: IC1.11 (IO26), R12.1, R13.2
PWM_DIM: IC1.9 (IO33), IC4.19 (PWM)
RTS: IC6.24 (RTS), Q3.2 (E), R37.1
RX: IC6.25 (RXD), R35.1, R39.2
RXD0: IC1.34 (RXD0), J7.3, R38.1
SENSOR_VIN: IC1.5 (SENSOR_VN)
SENSOR_VP: IC1.4 (SENSOR_VP)
SRV_SGN: IC5.4 (BY), R1.1
SRV_SGN_3.3V: IC1.36 (IO22), IC5.3 (A)
SW: C19.1, IC4.1 (SW_1), IC4.27 (SW_2), IC4.28 (SW_3), L1.2
TCK: IC1.16 (IO13), J8.3
TDI: IC1.14 (IO12), J8.2
TDO: IC1.23 (IO15), J8.4
TEMP_FAULT: IC1.7 (IO35), R28.2
TMP_SGN: IC1.12 (IO27), J6.3, R2.2
TMS: IC1.13 (IO14), J8.1
TX: IC6.26 (TXD), R34.1, R38.2
TXD0: IC1.35 (TXD0), J7.2, R39.1
VBUS: IC6.8 (VBUS), R29.2, R30.1

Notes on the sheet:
R4 is a pulldown when using the EN signal from a GPIO of the microcontroller, whereas R3, R7 and D3 are for when you just want EN to be always high.
DTR = 0, RTS = 1 -> IO0 is pulled down DTR = 1, RTS = 0 -> MCU_EN is pulled down DTR = 0, RTS = 0 -> MCU_EN is pulled high (elsewhere), IO0 is pulled high (internally) DTR = 1, RTS = 1 -> IO0 is pulled high, MCU_EN is pulled high
Need to double check and take notes of ALL VALUES
Do not place either R4, or R3, R7 and D3.
5-3.3V LDO
Water Pump
12-5V Buck Converter
Sensor Inputs
LED Driver
USB-to-UART Programmer
Fault LEDs
12V Power Input
Servo Motor
